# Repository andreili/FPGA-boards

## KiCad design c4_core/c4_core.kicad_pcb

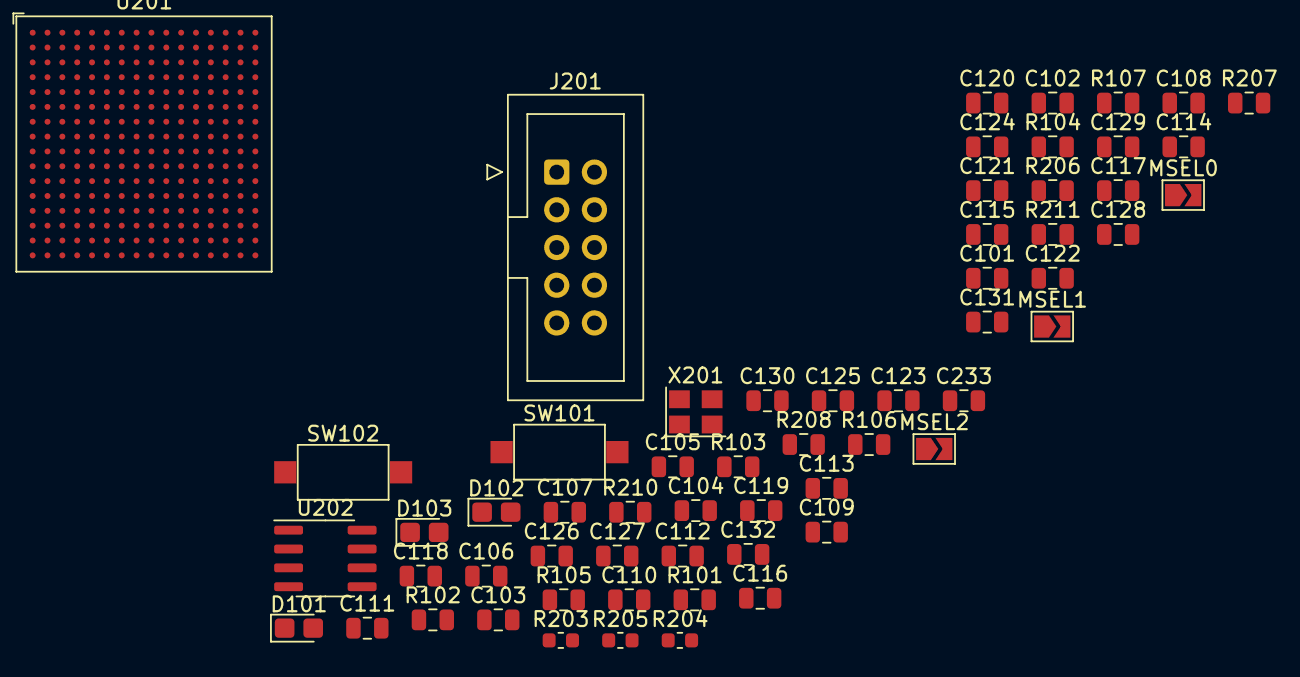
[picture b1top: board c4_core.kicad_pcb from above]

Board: 2 copper layers, 61 parts (1 on the bottom side), 24 nets, no tracks yet.

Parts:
C101, C102, C103, C104, C105, C106, C107, C108, C109, C110, C111, C112, C113, C114, C115, C116, C117, C118, C119, C120, C129, C130, C131, C132: 100nF; C_0805_2012Metric
C121, C122, C123, C124, C125, C126, C127, C128, C233: 22pF; C_0805_2012Metric
D101, D102, D103: LED; LED_0805_2012Metric_Castellated
J201: JTAG; IDC-Header_2x05_P2.54mm_Vertical
MSEL0, MSEL1, MSEL2: MSEL0; SolderJumper-2_P1.3mm_Open_TrianglePad1.0x1.5mm
R101, R102, R103, R107, R207, R208: 10k; R_0805_2012Metric
R104, R105, R106, R206, R210, R211: 1k; R_0805_2012Metric
R203, R204, R205: 10k; R_0603_1608Metric
SW101: NCONF; SW_SPST_CK_RS282G05A3
SW102: USER; SW_SPST_CK_RS282G05A3
U201: EP4CE6F17; BGA-256_17.0x17.0mm_Layout16x16_P1.0mm_Ball0.5mm_Pad0.4mm_N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
U202: M25P40; SOIC-8_3.9x4.9mm_P1.27mm
U203: MT48LC16M16A2; TSOP-II-54_22.2x10.16mm_P0.8mm
X201: 25MHz; Crystal_SMD_3225-4Pin_3.2x2.5mm

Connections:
+1V2: C103.2, C114.1, C121.1, C122.1, C123.1, C124.1, C125.1, C126.1, C127.1, C128.1, U201.D13 (VCCD_PLL2), U201.G6 (VCCINT), U201.G7 (VCCINT), U201.G8 (VCCINT), U201.G9 (VCCINT), U201.G10 (VCCINT), U201.H6 (VCCINT), U201.H11 (VCCINT), U201.K7 (VCCINT), U201.N4 (VCCD_PLL1)
+2V5: C110.1, C120.1, U201.F12 (VCCA2), U201.L5 (VCCA1)
+3V3: C101.1, C102.1, C104.1, C105.1, C106.1, C107.1, C108.1, C109.1, C111.1, C112.1, C113.1, C115.1, C116.1, C117.1, C118.1, C119.1, C129.1, C130.1, C131.1, C132.1, C233.1, J201.4, R101.2, R102.2, R103.2, R107.1, R203.1, R204.1, R205.1, R207.2, R208.2, R210.1, R211.1, U201.A1 (VCCIO8), U201.A16 (VCCIO7), U201.C4 (VCCIO8), U201.C7 (VCCIO8), U201.C10 (VCCIO7), U201.C13 (VCCIO7), U201.E3 (VCCIO1), U201.E14 (VCCIO6), U201.G3 (VCCIO1), U201.G14 (VCCIO6), U201.K3 (VCCIO2), U201.K14 (VCCIO5), U201.M3 (VCCIO2), U201.M14 (VCCIO5), U201.P4 (VCCIO3), U201.P7 (VCCIO3), U201.P10 (VCCIO4), U201.P13 (VCCIO4), U201.T1 (VCCIO3), U201.T16 (VCCIO4), U202.8 (VCC), U203.1 (VDD), U203.3 (VDDQ), U203.9 (VDDQ), U203.14 (VDD), U203.27 (VDD), U203.43 (VDDQ), U203.49 (VDDQ), X201.4 (Vcc)
ASDO: U201.C1 (IO_B1/ASDO), U202.5 (DQ0)
BTN: R107.2, SW102.1
DATA0: U201.H2 (IO_B1/DATA0), U202.2 (DQ1)
DCLK: U201.H1 (IO_B1/DCLK), U202.6 (C)
GND: C101.2, C102.2, C103.1, C104.2, C105.2, C106.2, C107.2, C108.2, C109.2, C110.2, C111.2, C112.2, C113.2, C114.2, C115.2, C116.2, C117.2, C118.2, C119.2, C120.2, C121.2, C122.2, C123.2, C124.2, C125.2, C126.2, C127.2, C128.2, C129.2, C130.2, C131.2, C132.2, C233.2, D101.1 (K), D102.1 (K), D103.1 (K), J201.2, J201.10, MSEL0.2 (B), MSEL1.2 (B), MSEL2.2 (B), R206.2, SW101.1, SW102.2, U201.B2 (GND), U201.B15 (GND), U201.C5 (GND), U201.C12 (GND), U201.D7 (GND), U201.D10 (GND), U201.E2 (GND), U201.E4 (GND), U201.E12 (GNDA2), U201.E13 (GND), U201.E15 (CLK4), U201.E16 (CLK5), U201.G4 (GND), U201.G13 (GND), U201.H7 (GND), U201.H8 (GND), U201.H9 (GND), U201.H10 (GND), U201.H15 (GND), U201.H16 (GND), U201.J3 (nCE), U201.J7 (GND), U201.J8 (GND), U201.J9 (GND), U201.J10 (GND), U201.K4 (GND), U201.K13 (GND), U201.M1 (CLK3), U201.M2 (CLK2), U201.M4 (GND), U201.M5 (GNDA1), U201.M13 (GND), U201.M15 (CLK6), U201.M16 (CLK7), U201.N7 (GND), U201.N10 (GND), U201.P5 (GND), U201.P12 (GND), U201.R2 (GND), U201.R15 (GND), U202.4 (VSS), U203.6 (VSSQ), U203.12 (VSSQ), U203.28 (VSS), U203.41 (VSS), U203.46 (VSSQ), U203.52 (VSSQ), U203.54 (VSS), X201.2 (GND)
MSEL0: MSEL0.1 (A), R203.2, U201.H13 (MSEL0)
MSEL1: MSEL1.1 (A), R204.2, U201.H12 (MSEL1)
MSEL2: MSEL2.1 (A), R205.2, U201.G12 (MSEL2)
NCONF: R102.1, SW101.2, U201.H5 (nCONFIG)
NCSO: U201.D2 (IO_B1/nCSO), U202.1 (S#)
unnamed: D101.2 (A), R104.2
unnamed: D102.2 (A), R105.2
unnamed: D103.2 (A), R106.2
unnamed: R101.1, U201.F4 (nSTATUS)
unnamed: R103.1, U201.H14 (CONF_DONE)
unnamed: R210.2, U202.3 (W#/VPP)
unnamed: R211.2, U202.7 (HOLD#)
TCK: J201.1, R206.1, U201.H3 (TCK)
TDI: J201.9, R207.1, U201.H4 (TDI)
TDO: J201.3, U201.J4 (TDO)
TMS: J201.5, R208.1, U201.J5 (TMS)

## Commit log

2021-08-06 Черновые версии схем, восстановленные по герберам.
2021-08-06 Добавлены герберы, по которым изготавливались платы.
